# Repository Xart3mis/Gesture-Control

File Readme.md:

# Too Lazy To Write A Readme rn lol #

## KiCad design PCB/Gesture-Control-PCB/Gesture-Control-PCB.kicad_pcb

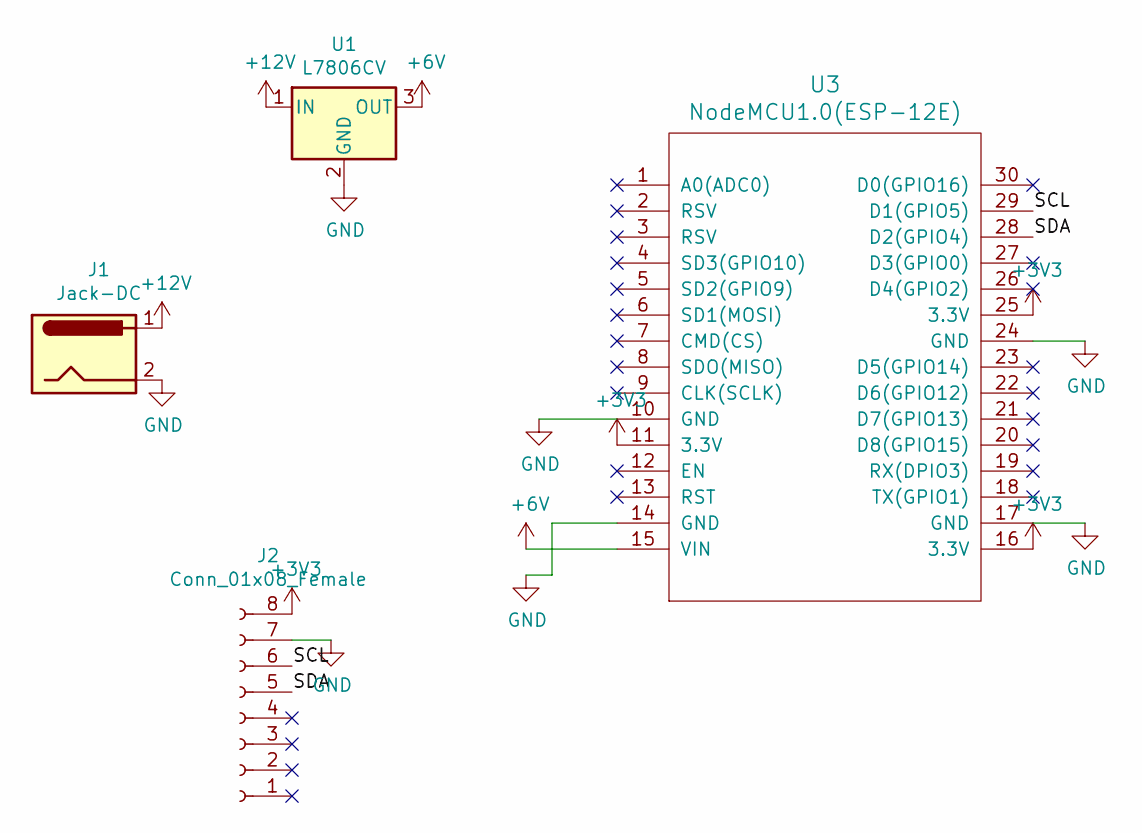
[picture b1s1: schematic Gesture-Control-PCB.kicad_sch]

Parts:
J1: Jack-DC; BarrelJack_Horizontal
J2: Conn_01x08_Female; PinSocket_1x08_P2.54mm_Vertical
U1: L7806CV; TO-220-3_Horizontal_TabDown
U3: NodeMCU1.0(ESP-12E); NodeMCU1.0(12-E)

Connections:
+3V3: J2.8, U3.11 (3.3V), U3.16 (3.3V), U3.25 (3.3V)
+6V: U1.3 (OUT), U3.15 (VIN)
+12V: J1.1, U1.1 (IN)
/SCL: J2.6, U3.29 (D1(GPIO5))
/SDA: J2.5, U3.28 (D2(GPIO4))
GND: J1.2, J2.7, U1.2 (GND), U3.10 (GND), U3.14 (GND), U3.17 (GND), U3.24 (GND)

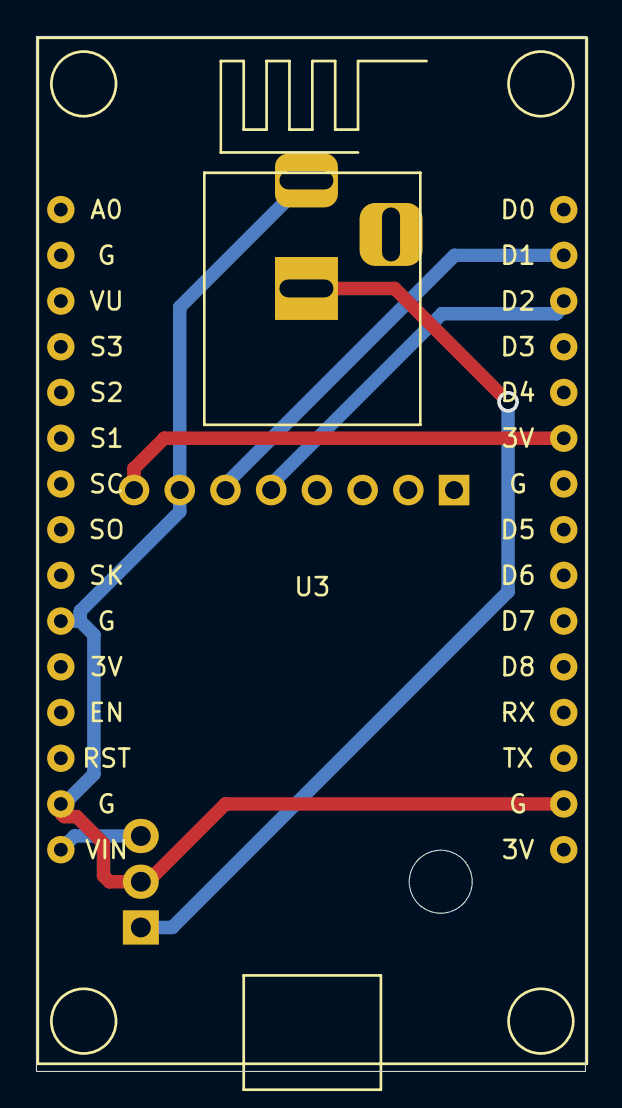
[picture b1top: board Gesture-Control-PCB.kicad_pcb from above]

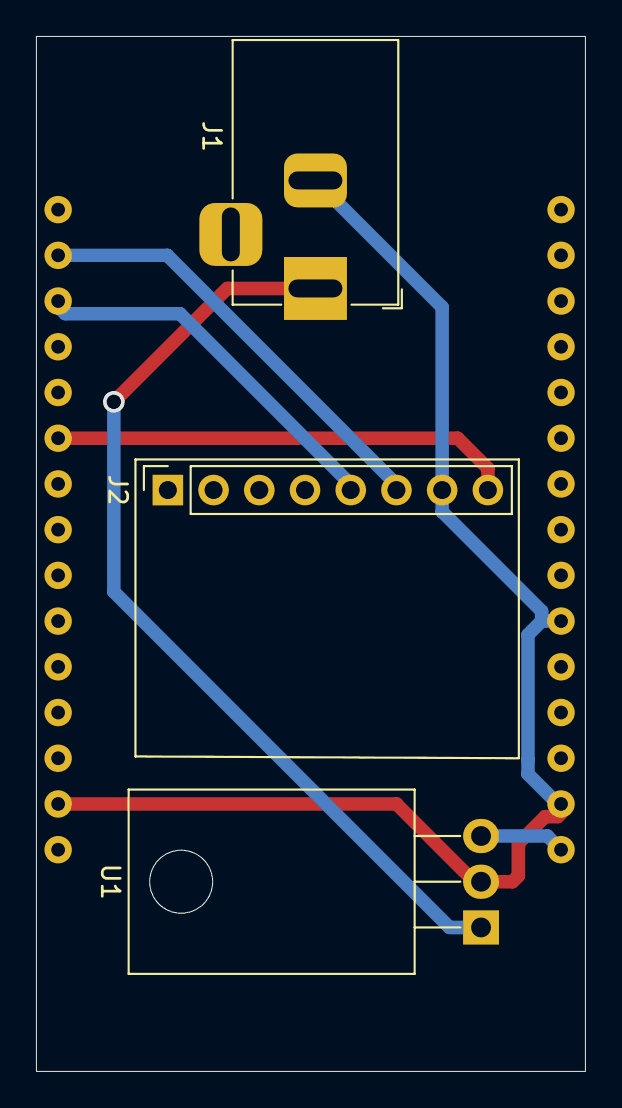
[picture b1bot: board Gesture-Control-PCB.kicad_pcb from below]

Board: 2 copper layers, 30.5 x 57.5 mm, 4 parts (3 on the bottom side), 6 nets.

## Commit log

2020-10-27 added counter and timer
2020-10-27 added blink led and increased baud rate
2020-10-27 baud rate
2020-10-28 added static ip and lowered message send time
2020-10-28 fixed counter and timer
2020-10-28 working on serialization
2020-10-28 might kms but at least it doesnt overflow mem now
2020-10-28 serialisation completed owo
2020-10-29 started integrating mpu9250 gyro
2020-10-29 fuck my life
2020-10-29 contemplating suicide
2020-10-29 TnT please work-
2020-11-05 for douva
2020-11-05 SUCKKK
2020-11-05 fuck mpu9250, like actually. fuck it
2020-11-14 remove douvas comment smh
2020-11-14 shit works LESHGETIT
2020-11-14 can now read from mpu6050 and send it to server
2020-11-15 send accel + gyro data instead of gyro/accel only
2020-11-15 websocket --> websocketserver
2020-11-15 proper json formatting and better logging
2020-11-15 remove asciichart dependency
2020-11-17 fixed formatting and rounding is 4 instead of 6
2020-11-17 removed T var, added a couple delays
2020-11-17 changed print formatting
2020-11-17 added PCB
2020-11-17 decrease size, fit all components under nodemcu
2020-11-17 add .vscode folder
2020-11-17 added readme
2020-11-17 enabled labels...
2020-11-18 removed one voltage regulator (lmao im a dummy)
2020-11-18 3v3 only connected once instead of 3 times
2020-11-18 fixed mpu socket and moved shit to bottom layer
2020-11-18 add output directory
2020-11-20 started work on smoothing
2020-11-20 added data smoothing and scaling + timer takes smoothing into account
2020-11-22 start working on kalman filtering for realtime smoothing
2020-11-22 kalman filtering test
2020-11-22 lower interval from 3ms to 0.05ms, added secrets.h to hide sensitive info
2020-11-22 integrated real-time kalman filtering instead of averaging
2020-11-22 add g and °/s to values when outputting to the console
2020-11-22 wrong dir lol
2020-11-22 add kalmanjs dependency to correct project lol
2020-11-22 add endpoint to secrets
2020-11-22 started work on keystroke injection using win32 api
2020-11-22 remove keystrokes.js file
2020-11-22 install sendkeys package
2020-11-22 remove sendkey dependency
2020-11-22 clear tests
2020-11-22 rename and clear tests.js file
2020-11-22 add nut-js dependency and fix test script
2020-11-23 update ArduinoJson library
2020-11-23 HID control test
2020-11-23 minor print format changes
2020-11-23 added automatic gyro calibration and removed unnescassary code to improve performance
2020-11-24 made code seksi
2020-11-25 move gyro calibration to seperate function
2020-11-25 added gyro threshholding and removed sendevery5seconds() function
2020-11-25 discard first 100 values, remove unused vars
2020-11-26 print more info
2020-11-26 move calibration to server side
2020-11-27 working from laptop, GAE
2020-11-27 added basic hid
2020-11-27 hid control on gyro x and y axis
2020-11-27 change keyboard delay to 0ms
2020-11-27 disable calibration
2020-11-29 server side gyro calibration
2020-11-29 now subtracts gyro offsets and prints on the same line
2020-11-29 contains gyro offsets
2020-11-29 add calibration script to npm
2020-11-29 remoce calibration and excess variables/comments
2020-11-29 remove README from gitignore
2020-12-02 generate BOM
2021-04-14 Added Secrets folder to gitignore
2021-04-14 replace let keyword with var
2021-04-14 js-polynomial-regression (i don't wanna talk about it)
2021-04-14 i am very not ok
2021-06-29 pcb shenanigans
2021-06-29 formatting
2021-06-29 ignore this
2021-06-29 trailing whitespace
2021-08-04 change Server folder structure and start work on golang server
2021-08-04 golang echo test
2021-09-23 readable
2022-02-07 spaces
